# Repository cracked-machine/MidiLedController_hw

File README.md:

# MIDI LED Controller (HW)

Required Kicad Hardware library: https://github.com/cracked-machine/KicadLibrary

For the corresponding SW repository:
[MidiLedController_sw](https://github.com/cracked-machine/MidiLedController_sw)

## Detailed Specifications:

Power Supply: 12V @ 2A (center positive).
Total quiescent current consumption: 85mA
Voltage output per channel: 10V
Current output per channel (Nom.): 
Total current consumption (Nom.): 
Current output per channel (fault limit): 
Total current consumption (fault limit): 2A

 ## Theory of Operation

 ### Power Supply overview

 A 12V DC input supply is stepped-down to 10V. Most of this will be used to power the LEDs. This is regulated down to provide 5V @ 100mA for the status leds. Additionally 3.3V @ 20mA is provided to the microcontroller.

### Output Channel overview

 MIDI Note-On commands are received and synchronised with the gating of 9 independant LED output channels.
 The brightness of all 9 channels can be adjusted simultaneously at the rear of the module.

 Fault protection monitors each output channel for short-circuit and over-current conditions.
 Fault protection is done on the _high side_ of the switch. MIDI data transmission is done on the _low side_ of the switch. i.e. the output channel anode remains at 5V (during normal operation) while the cathode is toggled by the Microcontroller GPIO.

 Individual output channel status is indicated with a tricolour LED.  See details on the Status LED sub-system below.

### Output channel status LED statemachine

Each output channel has a tricolour LED. As before a _green_ LED indicates that a load is connected to the output channel and power delivery to that channel is functioning as normal. An overcurrent or short circuit event is indicated by a _red_ LED and all power is disabled from that output channel.

A _blue_ LED indicates that no load is connected to the output channel. At this point, if MIDI data is still being transferred to that channel, the status LED will alternate between green and blue, in sync with the received MIDI data. This allows testing of the MIDI data transmission without needing to connect a load to the output channel.

When the load is connected, the status LED will **always** remain solid _green_.

A _red_ power fault status such as over current or short circuit will **always** override the other status colours.

### TODO

* upgrade SMPS to drop-in 3A components (TP56339, TPS54302, TPS54309). Considerations are Fsw/L1 size, Thermal Limits and cooling.
* Upgrade output series SOT23 transistor to higher currrent/thermal limit component...or to larger component (SOT223?)
* Test audio input triggering
* Additional pot control for reset delay (dual gang/ concetric pot)
* Upgrade DIP4 to DIP6

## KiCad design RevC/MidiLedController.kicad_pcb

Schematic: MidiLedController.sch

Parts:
C5, C26: 100pF; C_0805_2012Metric_Pad1.15x1.40mm_HandSolder; LcscNo C152892
C6, C28: 100n; C_0805_2012Metric_Pad1.15x1.40mm_HandSolder; LcscNo C94108
C32: 4.7u; C_0805_2012Metric_Pad1.15x1.40mm_HandSolder; LcscNo C87998
C33: 10n; C_0805_2012Metric_Pad1.15x1.40mm_HandSolder; LcscNo C107135
C34: 1u; C_0805_2012Metric_Pad1.15x1.40mm_HandSolder; LcscNo C376927
D2: 1N4148; D_SOD-323_HandSoldering; MouserNo 583-FM4005-T
D_STATUS1: LED_RAGB; LED_D5.0mm-4_RGB_Wide_Pins
D_STATUS_2, D_STATUS_3, D_STATUS_4, D_STATUS_5, D_STATUS_6, D_STATUS_7, D_STATUS_8, D_STATUS_9: LED_RAGB; LED_D5.0mm-4_RGB_Wide_Pins
J1: Molex 2Way KK254; PinHeader_1x05_P2.54mm_Vertical
J12: Barrel_Jack; BarrelJack_Horizontal
J_AUX1: Conn_01x04; PinHeader_1x04_P2.54mm_Vertical
J_MIDI_IN1: DIN-5; RS_5P180_DIN5_SOCKET_WSHIELD
J_OUT1, J_OUT2, J_OUT3, J_OUT4, J_OUT5, J_OUT6, J_OUT7, J_OUT8, J_OUT9: Barrel_Jack_Switch; BarrelJack_Horizontal
R1: 10K; R_0805_2012Metric_Pad1.15x1.40mm_HandSolder; LcscNo C115295
R4: 220R; R_0805_2012Metric_Pad1.15x1.40mm_HandSolder; MouserNo 71-CRCW0805220RFKEAC
R9: 4K7; R_0805_2012Metric_Pad1.15x1.40mm_HandSolder; MouserNo 279-CRGP0805F270R
R25, R74: 100R; R_0805_2012Metric_Pad1.15x1.40mm_HandSolder; LcscNo C106949
R119, R120, R121, R122: 1K; R_0805_2012Metric_Pad1.15x1.40mm_HandSolder; LcscNo C25623
RV1: PTH901; MouserNo 652-PTH901-030S-103B
SW1: SW_DIP_x04; SW_DIP_SPSTx04_Slide_6.7x11.72mm_W7.62mm_P2.54mm_LowProfile
SW2: SW_SPST; SW_Tactile_SPST_Angled_PTS645Vx31-2LFS
TP1, TP3, TP4, TP7, TP19, TP42, TP44, TP46, TP50: TestPoint; TestPoint_Pad_1.0x1.0mm
U19: H11L1; SMDIP-6_W9.53mm
U20: STM32F051K8Tx; LQFP-32_7x7mm_P0.8mm; MouserNo 511-STM32F051K8T6

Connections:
+3.3VA: C33.1, C34.1, U20.5 (VDDA); also elsewhere on the board
+3V3: C6.1, C28.1, C32.1, J1.1, R119.1, R120.1, R121.1, R122.1, RV1.3, RV1.6, U20.1 (VDD), U20.17 (VDD); also elsewhere on the board
+5V: J_AUX1.4, R9.1, U19.6; also elsewhere on the board
/ADC_IN0: C26.2, R74.2, TP1.1, U20.6 (PA0)
/ADC_IN1: C5.2, R25.2, TP3.1, U20.7 (PA1)
/ADC_IN2: J_AUX1.2, U20.8 (PA2)
/ADC_IN3: J_AUX1.1, U20.9 (PA3)
/CH1_PWR: J_OUT1.1; also elsewhere on the board
/CH2_PWR: J_OUT2.1; also elsewhere on the board
/CH3_PWR: J_OUT3.1; also elsewhere on the board
/CH4_PWR: J_OUT4.1; also elsewhere on the board
/CH5_PWR: J_OUT5.1; also elsewhere on the board
/CH6_PWR: J_OUT6.1; also elsewhere on the board
/CH7_PWR: J_OUT7.1; also elsewhere on the board
/CH8_PWR: J_OUT8.1; also elsewhere on the board
/CH9_PWR: J_OUT9.1; also elsewhere on the board
/CONFIG1: R119.2, SW1.8, U20.10 (PA4)
/CONFIG2: R120.2, SW1.7, U20.11 (PA5)
/CONFIG3: R121.2, SW1.6, U20.12 (PA6)
/CONFIG4: R122.2, SW1.5, U20.13 (PA7)
/ChannelNMOS1/CH_CATHODE: J_OUT1.2; also elsewhere on the board
/ChannelNMOS2/CH_CATHODE: J_OUT2.2; also elsewhere on the board
/ChannelNMOS3/CH_CATHODE: J_OUT3.2; also elsewhere on the board
/ChannelNMOS4/CH_CATHODE: J_OUT4.2; also elsewhere on the board
/ChannelNMOS5/CH_CATHODE: J_OUT5.2; also elsewhere on the board
/ChannelNMOS6/CH_CATHODE: J_OUT6.2; also elsewhere on the board
/ChannelNMOS7/CH_CATHODE: J_OUT7.2; also elsewhere on the board
/ChannelNMOS8/CH_CATHODE: J_OUT8.2; also elsewhere on the board
/ChannelNMOS9/CH_CATHODE: J_OUT9.2; also elsewhere on the board
/ChannelStatusLED1/CH_DISABLE_SW: J_OUT1.3; also elsewhere on the board
/ChannelStatusLED1/CH_LED1: D_STATUS1.1 (RK); also elsewhere on the board
/ChannelStatusLED1/CH_LED3: D_STATUS1.3 (GK); also elsewhere on the board
/ChannelStatusLED1/CH_LED4: D_STATUS1.4 (BK); also elsewhere on the board
/ChannelStatusLED2/CH_DISABLE_SW: J_OUT2.3; also elsewhere on the board
/ChannelStatusLED2/CH_LED1: D_STATUS_2.1 (RK); also elsewhere on the board
/ChannelStatusLED2/CH_LED3: D_STATUS_2.3 (GK); also elsewhere on the board
/ChannelStatusLED2/CH_LED4: D_STATUS_2.4 (BK); also elsewhere on the board
/ChannelStatusLED3/CH_DISABLE_SW: J_OUT3.3; also elsewhere on the board
/ChannelStatusLED3/CH_LED1: D_STATUS_3.1 (RK); also elsewhere on the board
/ChannelStatusLED3/CH_LED3: D_STATUS_3.3 (GK); also elsewhere on the board
/ChannelStatusLED3/CH_LED4: D_STATUS_3.4 (BK); also elsewhere on the board
/ChannelStatusLED4/CH_DISABLE_SW: J_OUT4.3; also elsewhere on the board
/ChannelStatusLED4/CH_LED1: D_STATUS_4.1 (RK); also elsewhere on the board
/ChannelStatusLED4/CH_LED3: D_STATUS_4.3 (GK); also elsewhere on the board
/ChannelStatusLED4/CH_LED4: D_STATUS_4.4 (BK); also elsewhere on the board
/ChannelStatusLED5/CH_DISABLE_SW: J_OUT5.3; also elsewhere on the board
/ChannelStatusLED5/CH_LED1: D_STATUS_5.1 (RK); also elsewhere on the board
/ChannelStatusLED5/CH_LED3: D_STATUS_5.3 (GK); also elsewhere on the board
/ChannelStatusLED5/CH_LED4: D_STATUS_5.4 (BK); also elsewhere on the board
/ChannelStatusLED6/CH_DISABLE_SW: J_OUT6.3; also elsewhere on the board
/ChannelStatusLED6/CH_LED1: D_STATUS_6.1 (RK); also elsewhere on the board
/ChannelStatusLED6/CH_LED3: D_STATUS_6.3 (GK); also elsewhere on the board
/ChannelStatusLED6/CH_LED4: D_STATUS_6.4 (BK); also elsewhere on the board
/ChannelStatusLED7/CH_DISABLE_SW: J_OUT7.3; also elsewhere on the board
/ChannelStatusLED7/CH_LED1: D_STATUS_7.1 (RK); also elsewhere on the board
/ChannelStatusLED7/CH_LED3: D_STATUS_7.3 (GK); also elsewhere on the board
/ChannelStatusLED7/CH_LED4: D_STATUS_7.4 (BK); also elsewhere on the board
/ChannelStatusLED8/CH_DISABLE_SW: J_OUT8.3; also elsewhere on the board
/ChannelStatusLED8/CH_LED1: D_STATUS_8.1 (RK); also elsewhere on the board
/ChannelStatusLED8/CH_LED3: D_STATUS_8.3 (GK); also elsewhere on the board
/ChannelStatusLED8/CH_LED4: D_STATUS_8.4 (BK); also elsewhere on the board
/ChannelStatusLED9/CH_DISABLE_SW: J_OUT9.3; also elsewhere on the board
/ChannelStatusLED9/CH_LED1: D_STATUS_9.1 (RK); also elsewhere on the board
/ChannelStatusLED9/CH_LED3: D_STATUS_9.3 (GK); also elsewhere on the board
/ChannelStatusLED9/CH_LED4: D_STATUS_9.4 (BK); also elsewhere on the board
/MIDI_RX: R9.2, TP4.1, U19.5, U20.30 (PB7)
/NRST: J1.5, U20.4 (NRST)
/PowerSupply/ENSW: SW2.2 (B); also elsewhere on the board
/PowerSupply/VIN: J12.1; also elsewhere on the board
/STATUS1_ANODE: D_STATUS1.2 (A); also elsewhere on the board
/STATUS2_ANODE: D_STATUS_2.2 (A); also elsewhere on the board
/STATUS3_ANODE: D_STATUS_3.2 (A); also elsewhere on the board
/STATUS4_ANODE: D_STATUS_4.2 (A); also elsewhere on the board
/STATUS5_ANODE: D_STATUS_5.2 (A); also elsewhere on the board
/STATUS6_ANODE: D_STATUS_6.2 (A); also elsewhere on the board
/STATUS7_ANODE: D_STATUS_7.2 (A); also elsewhere on the board
/STATUS8_ANODE: D_STATUS_8.2 (A); also elsewhere on the board
/STATUS9_ANODE: D_STATUS_9.2 (A); also elsewhere on the board
/SWCLK: J1.2, U20.24 (PA14)
/SWDIO: J1.4, U20.23 (PA13)
/TIM1_CH1: U20.18 (PA8); also elsewhere on the board
/TIM1_CH2: U20.19 (PA9); also elsewhere on the board
/TIM1_CH3: U20.20 (PA10); also elsewhere on the board
/TIM2_CH1: U20.25 (PA15); also elsewhere on the board
/TIM2_CH2: U20.26 (PB3); also elsewhere on the board
/TIM3_CH1: U20.27 (PB4); also elsewhere on the board
/TIM3_CH2: U20.28 (PB5); also elsewhere on the board
/TIM3_CH3: U20.14 (PB0); also elsewhere on the board
/TIM3_CH4: U20.15 (PB1); also elsewhere on the board
GNDS: C5.1, C6.2, C26.1, C28.2, C32.2, C33.2, C34.2, J1.3, J12.2, J_AUX1.3, R1.2, RV1.1, RV1.4, SW1.1, SW1.2, SW1.3, SW1.4, SW2.1 (A), TP19.1, TP42.1, TP44.1, TP46.1, TP50.1, U19.4, U20.16 (VSS), U20.32 (VSS); also elsewhere on the board
unnamed: D2.1 (K), R4.1, U19.1
unnamed: D2.2 (A), J_MIDI_IN1.5, U19.3
unnamed: J_MIDI_IN1.4, R4.2, TP7.1
unnamed: R1.1, U20.31 (BOOT0)
unnamed: R25.1, RV1.5
unnamed: R74.1, RV1.2

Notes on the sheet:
ICSP
MicroController
USART TX (NOT USED)
MIDI Input
Power Supply / Regulation
Brightness Control
5-12V POWER INPUT
Output Channel 1
Output Channel 2
Output Channel 3
Output Channel 4
Output Channel 5
Output Channel 6
Output Channel 7
Output Channel 8
Output Channel 9
(RED) (ANODE) (GREEN) (BLUE)
LED STRIP
change to 270R if using 6N137
Config Switches

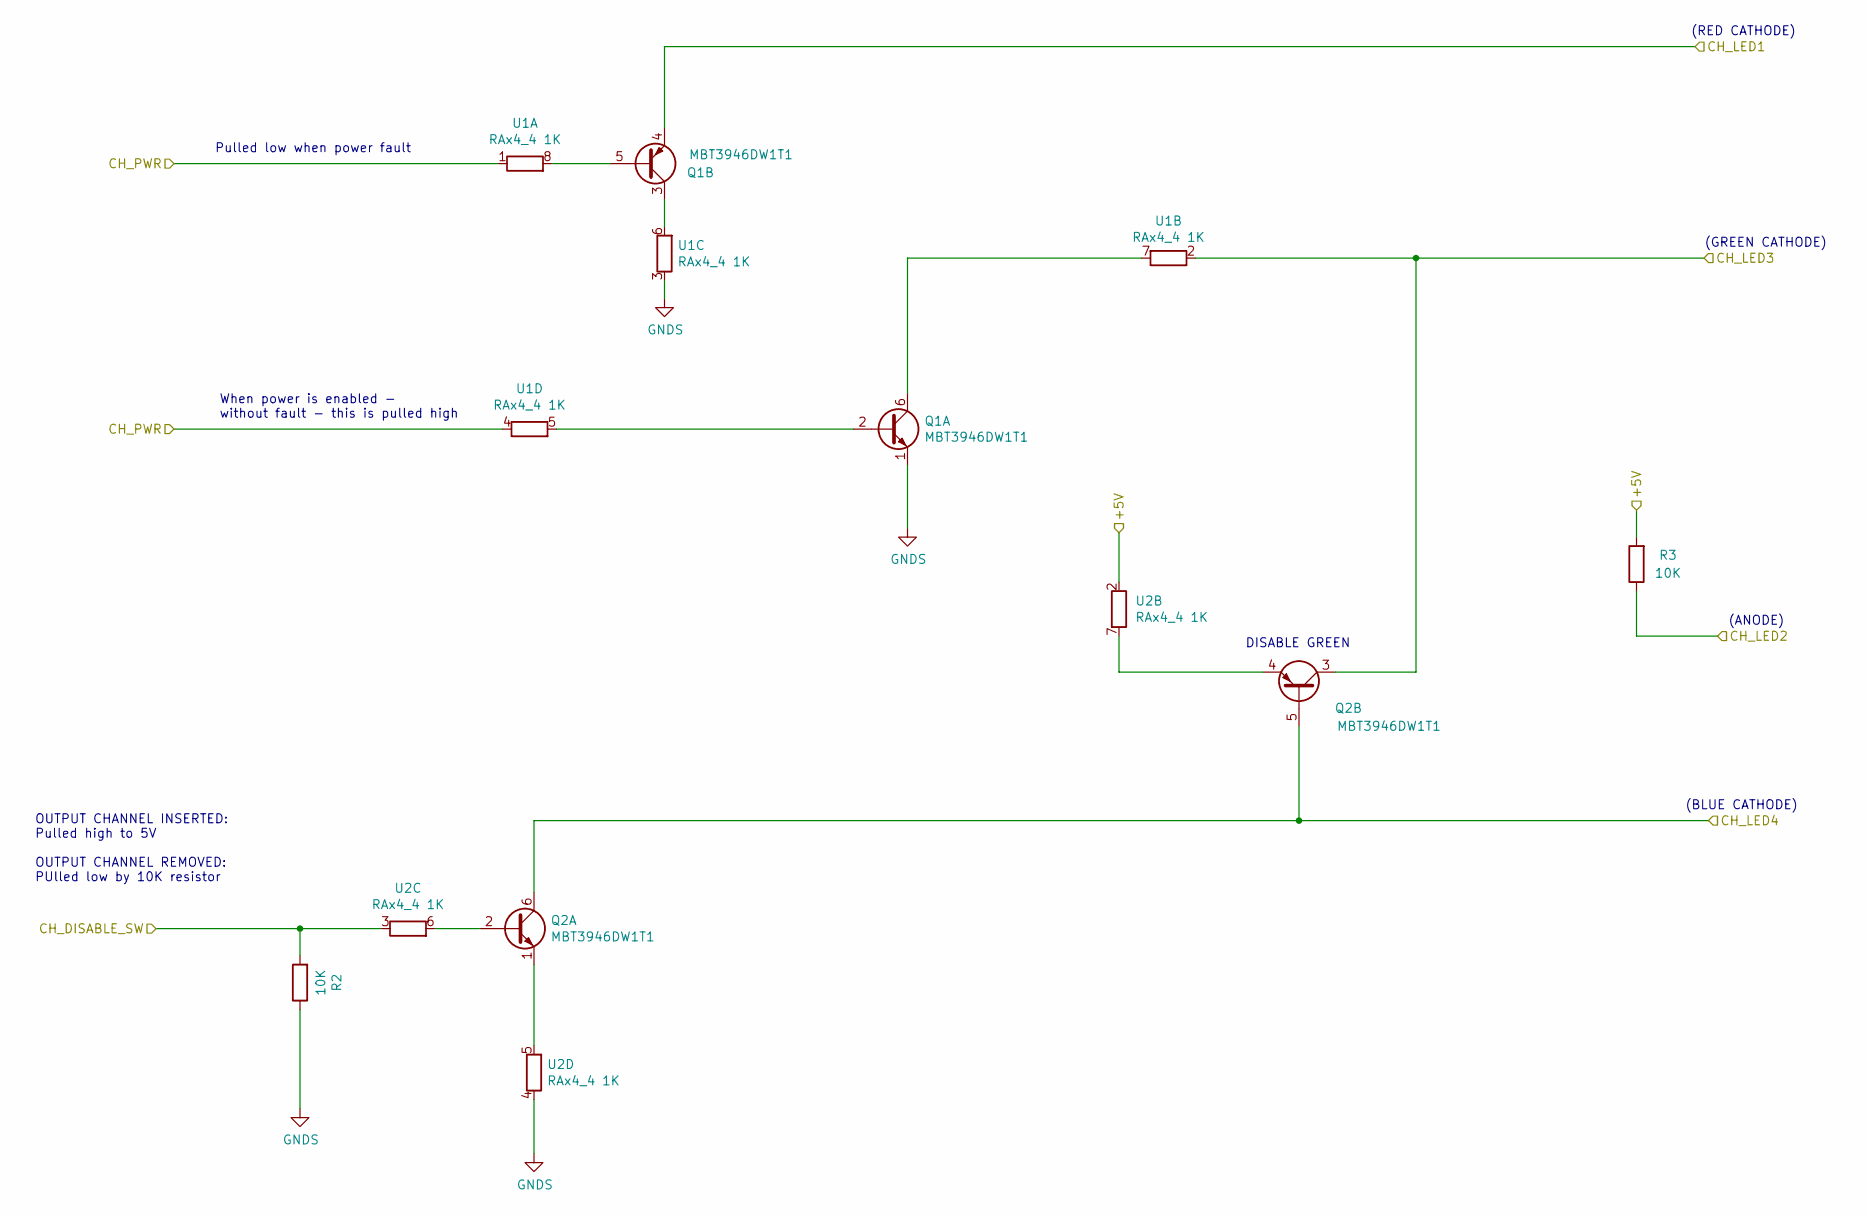
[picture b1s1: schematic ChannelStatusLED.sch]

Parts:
Q1, Q2: MBT3946DW1T1; SOT-363_SC-70-6
R2, R3: 10K; R_0805_2012Metric_Pad1.15x1.40mm_HandSolder; LcscNo C115295
U1, U2: RAx4_4 1K; R_Array_Convex_4x0603; LcscNo C396839

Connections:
+5V: R3.2, U2.2; also elsewhere on the board
/CH1_PWR: U1.1, U1.4; also elsewhere on the board
/ChannelStatusLED1/CH_DISABLE_SW: R2.2, U2.3; also elsewhere on the board
/ChannelStatusLED1/CH_LED1: Q1.4 (E2); also elsewhere on the board
/ChannelStatusLED1/CH_LED3: Q2.3 (C2), U1.2; also elsewhere on the board
/ChannelStatusLED1/CH_LED4: Q2.5 (B2), Q2.6 (C1); also elsewhere on the board
/STATUS1_ANODE: R3.1; also elsewhere on the board
GNDS: Q1.1 (E1), R2.1, U1.3, U2.4; also elsewhere on the board
unnamed: Q1.2 (B1), U1.5
unnamed: Q1.3 (C2), U1.6
unnamed: Q1.5 (B2), U1.8
unnamed: Q1.6 (C1), U1.7
unnamed: Q2.1 (E1), U2.5
unnamed: Q2.2 (B1), U2.6
unnamed: Q2.4 (E2), U2.7

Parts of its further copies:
Q3, Q4, Q5, Q6, Q7, Q8, Q9, Q10, Q11, Q12, Q13, Q14, Q15, Q16, Q17, Q18: MBT3946DW1T1; SOT-363_SC-70-6
R5, R6, R7, R8, R10, R11, R12, R14, R17, R18, R19, R20, R21, R22, R23, R24: 10K; R_0805_2012Metric_Pad1.15x1.40mm_HandSolder; LcscNo C115295
U3, U4, U5, U6, U7, U8, U9, U10, U11, U12, U13, U14, U15, U16, U17, U18: RAx4_4 1K; R_Array_Convex_4x0603; LcscNo C396839

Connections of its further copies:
+5V: R6.2, R8.2, R11.2, R14.2, R18.2, R20.2, R22.2, R24.2, U4.1, U4.2, U6.1, U6.2, U8.1, U8.2, U10.1, U10.2, U12.1, U12.2, U14.1, U14.2, U16.1, U16.2, U18.1, U18.2; also elsewhere on the board
/CH2_PWR: U3.1, U3.4; also elsewhere on the board
/CH3_PWR: U5.1, U5.4; also elsewhere on the board
/CH4_PWR: U7.1, U7.4; also elsewhere on the board
/CH5_PWR: U9.1, U9.4; also elsewhere on the board
/CH6_PWR: U11.1, U11.4; also elsewhere on the board
/CH7_PWR: U13.1, U13.4; also elsewhere on the board
/CH8_PWR: U15.1, U15.4; also elsewhere on the board
/CH9_PWR: U17.1, U17.4; also elsewhere on the board
/ChannelNMOS2/CH_CATHODE: U4.8; also elsewhere on the board
/ChannelNMOS3/CH_CATHODE: U6.8; also elsewhere on the board
/ChannelNMOS4/CH_CATHODE: U8.8; also elsewhere on the board
/ChannelNMOS5/CH_CATHODE: U10.8; also elsewhere on the board
/ChannelNMOS6/CH_CATHODE: U12.8; also elsewhere on the board
/ChannelNMOS7/CH_CATHODE: U14.8; also elsewhere on the board
/ChannelNMOS8/CH_CATHODE: U16.8; also elsewhere on the board
/ChannelNMOS9/CH_CATHODE: U18.8; also elsewhere on the board
/ChannelStatusLED2/CH_DISABLE_SW: R5.2, U4.3; also elsewhere on the board
/ChannelStatusLED2/CH_LED1: Q3.4 (E2); also elsewhere on the board
/ChannelStatusLED2/CH_LED3: Q4.3 (C2), U3.2; also elsewhere on the board
/ChannelStatusLED2/CH_LED4: Q4.5 (B2), Q4.6 (C1); also elsewhere on the board
/ChannelStatusLED3/CH_DISABLE_SW: R7.2, U6.3; also elsewhere on the board
/ChannelStatusLED3/CH_LED1: Q5.4 (E2); also elsewhere on the board
/ChannelStatusLED3/CH_LED3: Q6.3 (C2), U5.2; also elsewhere on the board
/ChannelStatusLED3/CH_LED4: Q6.5 (B2), Q6.6 (C1); also elsewhere on the board
/ChannelStatusLED4/CH_DISABLE_SW: R10.2, U8.3; also elsewhere on the board
/ChannelStatusLED4/CH_LED1: Q7.4 (E2); also elsewhere on the board
/ChannelStatusLED4/CH_LED3: Q8.3 (C2), U7.2; also elsewhere on the board
/ChannelStatusLED4/CH_LED4: Q8.5 (B2), Q8.6 (C1); also elsewhere on the board
/ChannelStatusLED5/CH_DISABLE_SW: R12.2, U10.3; also elsewhere on the board
/ChannelStatusLED5/CH_LED1: Q9.4 (E2); also elsewhere on the board
/ChannelStatusLED5/CH_LED3: Q10.3 (C2), U9.2; also elsewhere on the board
/ChannelStatusLED5/CH_LED4: Q10.5 (B2), Q10.6 (C1); also elsewhere on the board
/ChannelStatusLED6/CH_DISABLE_SW: R17.2, U12.3; also elsewhere on the board
/ChannelStatusLED6/CH_LED1: Q11.4 (E2); also elsewhere on the board
/ChannelStatusLED6/CH_LED3: Q12.3 (C2), U11.2; also elsewhere on the board
/ChannelStatusLED6/CH_LED4: Q12.5 (B2), Q12.6 (C1); also elsewhere on the board
/ChannelStatusLED7/CH_DISABLE_SW: R19.2, U14.3; also elsewhere on the board
/ChannelStatusLED7/CH_LED1: Q13.4 (E2); also elsewhere on the board
/ChannelStatusLED7/CH_LED3: Q14.3 (C2), U13.2; also elsewhere on the board
/ChannelStatusLED7/CH_LED4: Q14.5 (B2), Q14.6 (C1); also elsewhere on the board
/ChannelStatusLED8/CH_DISABLE_SW: R21.2, U16.3; also elsewhere on the board
/ChannelStatusLED8/CH_LED1: Q15.4 (E2); also elsewhere on the board
/ChannelStatusLED8/CH_LED3: Q16.3 (C2), U15.2; also elsewhere on the board
/ChannelStatusLED8/CH_LED4: Q16.5 (B2), Q16.6 (C1); also elsewhere on the board
/ChannelStatusLED9/CH_DISABLE_SW: R23.2, U18.3; also elsewhere on the board
/ChannelStatusLED9/CH_LED1: Q17.4 (E2); also elsewhere on the board
/ChannelStatusLED9/CH_LED3: Q18.3 (C2), U17.2; also elsewhere on the board
/ChannelStatusLED9/CH_LED4: Q18.5 (B2), Q18.6 (C1); also elsewhere on the board
/STATUS2_ANODE: R6.1; also elsewhere on the board
/STATUS3_ANODE: R8.1; also elsewhere on the board
/STATUS4_ANODE: R11.1; also elsewhere on the board
/STATUS5_ANODE: R14.1; also elsewhere on the board
/STATUS6_ANODE: R18.1; also elsewhere on the board
/STATUS7_ANODE: R20.1; also elsewhere on the board
/STATUS8_ANODE: R22.1; also elsewhere on the board
/STATUS9_ANODE: R24.1; also elsewhere on the board
GNDS: Q3.1 (E1), Q5.1 (E1), Q7.1 (E1), Q9.1 (E1), Q11.1 (E1), Q13.1 (E1), Q15.1 (E1), Q17.1 (E1), R5.1, R7.1, R10.1, R12.1, R17.1, R19.1, R21.1, R23.1, U3.3, U4.4, U5.3, U6.4, U7.3, U8.4, U9.3, U10.4, U11.3, U12.4, U13.3, U14.4, U15.3, U16.4, U17.3, U18.4; also elsewhere on the board
unnamed: Q3.2 (B1), U3.5
unnamed: Q3.3 (C2), U3.6
unnamed: Q3.5 (B2), U3.8
unnamed: Q3.6 (C1), U3.7
unnamed: Q4.1 (E1), U4.5
unnamed: Q4.2 (B1), U4.6
unnamed: Q4.4 (E2), U4.7
unnamed: Q5.2 (B1), U5.5
unnamed: Q5.3 (C2), U5.6
unnamed: Q5.5 (B2), U5.8
unnamed: Q5.6 (C1), U5.7
unnamed: Q6.1 (E1), U6.5
unnamed: Q6.2 (B1), U6.6
unnamed: Q6.4 (E2), U6.7
unnamed: Q7.2 (B1), U7.5
unnamed: Q7.3 (C2), U7.6
unnamed: Q7.5 (B2), U7.8
unnamed: Q7.6 (C1), U7.7
unnamed: Q8.1 (E1), U8.5
unnamed: Q8.2 (B1), U8.6
unnamed: Q8.4 (E2), U8.7
unnamed: Q9.2 (B1), U9.5
unnamed: Q9.3 (C2), U9.6
unnamed: Q9.5 (B2), U9.8
unnamed: Q9.6 (C1), U9.7
unnamed: Q10.1 (E1), U10.5
unnamed: Q10.2 (B1), U10.6
unnamed: Q10.4 (E2), U10.7
unnamed: Q11.2 (B1), U11.5
unnamed: Q11.3 (C2), U11.6
unnamed: Q11.5 (B2), U11.8
unnamed: Q11.6 (C1), U11.7
unnamed: Q12.1 (E1), U12.5
unnamed: Q12.2 (B1), U12.6
unnamed: Q12.4 (E2), U12.7
unnamed: Q13.2 (B1), U13.5
unnamed: Q13.3 (C2), U13.6
unnamed: Q13.5 (B2), U13.8
unnamed: Q13.6 (C1), U13.7
unnamed: Q14.1 (E1), U14.5
unnamed: Q14.2 (B1), U14.6
unnamed: Q14.4 (E2), U14.7
unnamed: Q15.2 (B1), U15.5
unnamed: Q15.3 (C2), U15.6
unnamed: Q15.5 (B2), U15.8
unnamed: Q15.6 (C1), U15.7
unnamed: Q16.1 (E1), U16.5
unnamed: Q16.2 (B1), U16.6
unnamed: Q16.4 (E2), U16.7
unnamed: Q17.2 (B1), U17.5
unnamed: Q17.3 (C2), U17.6
unnamed: Q17.5 (B2), U17.8
unnamed: Q17.6 (C1), U17.7
unnamed: Q18.1 (E1), U18.5
unnamed: Q18.2 (B1), U18.6
unnamed: Q18.4 (E2), U18.7

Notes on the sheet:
When power is enabled - without fault - this is pulled high
(BLUE CATHODE)
(ANODE)
(GREEN CATHODE)
Pulled low when power fault
(RED CATHODE)
DISABLE GREEN
OUTPUT CHANNEL INSERTED: Pulled high to 5V OUTPUT CHANNEL REMOVED: PUlled low by 10K resistor

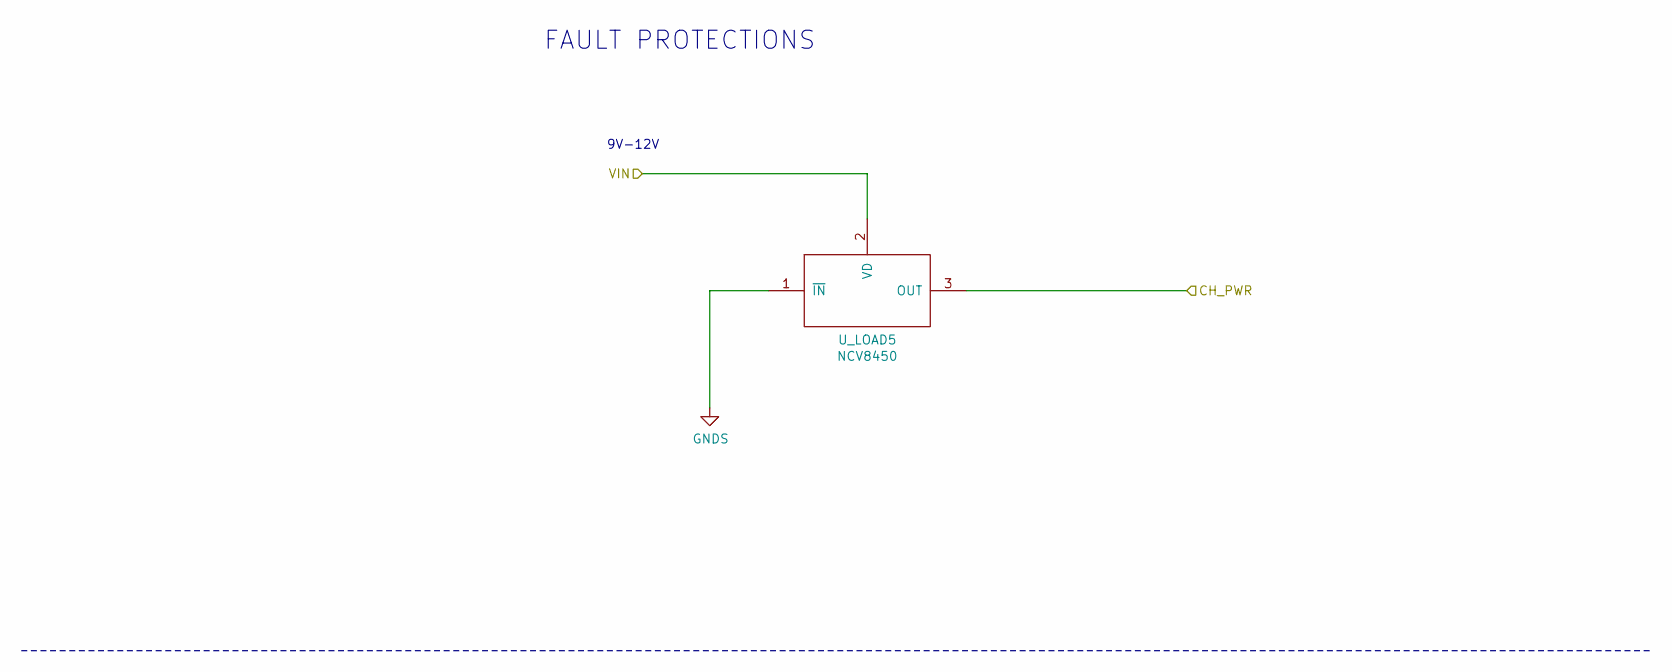
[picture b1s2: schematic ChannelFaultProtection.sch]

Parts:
U_LOAD2: NCV8450; SOT-223-3_TabPin2; LcscNo C100028

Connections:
/CH2_PWR: U_LOAD2.3 (OUT); also elsewhere on the board
GNDS: U_LOAD2.1 (~IN); also elsewhere on the board
VPP: U_LOAD2.2 (VD); also elsewhere on the board

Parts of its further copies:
U_LOAD1, U_LOAD3, U_LOAD4, U_LOAD5, U_LOAD6, U_LOAD7, U_LOAD8, U_LOAD9: NCV8450; SOT-223-3_TabPin2; LcscNo C100028

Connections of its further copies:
/CH1_PWR: U_LOAD1.3 (OUT); also elsewhere on the board
/CH3_PWR: U_LOAD3.3 (OUT); also elsewhere on the board
/CH4_PWR: U_LOAD4.3 (OUT); also elsewhere on the board
/CH5_PWR: U_LOAD5.3 (OUT); also elsewhere on the board
/CH6_PWR: U_LOAD6.3 (OUT); also elsewhere on the board
/CH7_PWR: U_LOAD7.3 (OUT); also elsewhere on the board
/CH8_PWR: U_LOAD8.3 (OUT); also elsewhere on the board
/CH9_PWR: U_LOAD9.3 (OUT); also elsewhere on the board
GNDS: U_LOAD1.1 (~IN), U_LOAD3.1 (~IN), U_LOAD4.1 (~IN), U_LOAD5.1 (~IN), U_LOAD6.1 (~IN), U_LOAD7.1 (~IN), U_LOAD8.1 (~IN), U_LOAD9.1 (~IN); also elsewhere on the board
VPP: U_LOAD1.2 (VD), U_LOAD3.2 (VD), U_LOAD4.2 (VD), U_LOAD5.2 (VD), U_LOAD6.2 (VD), U_LOAD7.2 (VD), U_LOAD8.2 (VD), U_LOAD9.2 (VD); also elsewhere on the board

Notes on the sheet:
9V-12V
FAULT PROTECTIONS

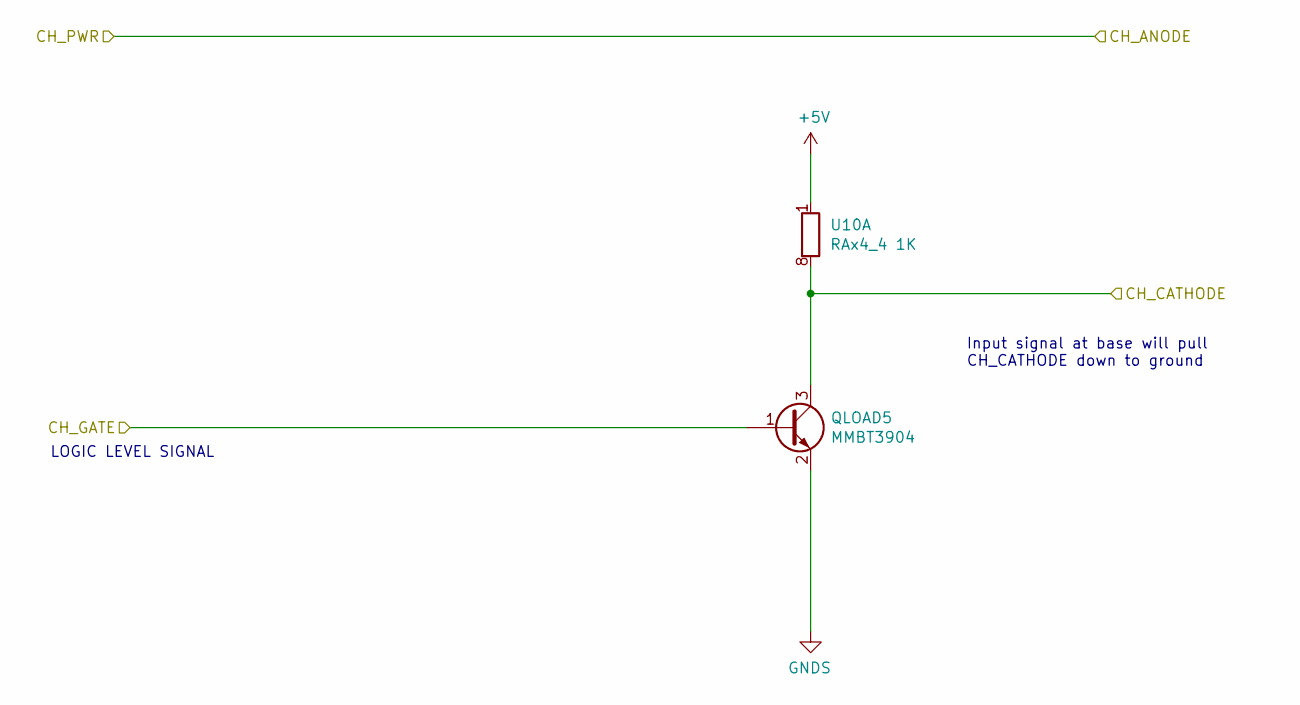
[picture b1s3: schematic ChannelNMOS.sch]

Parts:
QLOAD1: MMBT3904; SOT-23; LcscNo C20526
U2: RAx4_4 1K; R_Array_Convex_4x0603

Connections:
+5V: U2.1; also elsewhere on the board
/ChannelNMOS1/CH_CATHODE: QLOAD1.3 (C), U2.8; also elsewhere on the board
/TIM2_CH1: QLOAD1.1 (B); also elsewhere on the board
GNDS: QLOAD1.2 (E); also elsewhere on the board

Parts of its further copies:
QLOAD2, QLOAD3, QLOAD4, QLOAD5, QLOAD6, QLOAD7, QLOAD8, QLOAD9: MMBT3904; SOT-23; LcscNo C20526
U4, U6, U8, U10, U12, U14, U16, U18: RAx4_4 1K; R_Array_Convex_4x0603

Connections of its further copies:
+5V: U4.1, U4.2, U6.1, U6.2, U8.1, U8.2, U10.1, U10.2, U12.1, U12.2, U14.1, U14.2, U16.1, U16.2, U18.1, U18.2; also elsewhere on the board
/ChannelNMOS2/CH_CATHODE: QLOAD2.3 (C), U4.8; also elsewhere on the board
/ChannelNMOS3/CH_CATHODE: QLOAD3.3 (C), U6.8; also elsewhere on the board
/ChannelNMOS4/CH_CATHODE: QLOAD4.3 (C), U8.8; also elsewhere on the board
/ChannelNMOS5/CH_CATHODE: QLOAD5.3 (C), U10.8; also elsewhere on the board
/ChannelNMOS6/CH_CATHODE: QLOAD6.3 (C), U12.8; also elsewhere on the board
/ChannelNMOS7/CH_CATHODE: QLOAD7.3 (C), U14.8; also elsewhere on the board
/ChannelNMOS8/CH_CATHODE: QLOAD8.3 (C), U16.8; also elsewhere on the board
/ChannelNMOS9/CH_CATHODE: QLOAD9.3 (C), U18.8; also elsewhere on the board
/ChannelStatusLED2/CH_DISABLE_SW: U4.3; also elsewhere on the board
/ChannelStatusLED3/CH_DISABLE_SW: U6.3; also elsewhere on the board
/ChannelStatusLED4/CH_DISABLE_SW: U8.3; also elsewhere on the board
/ChannelStatusLED5/CH_DISABLE_SW: U10.3; also elsewhere on the board
/ChannelStatusLED6/CH_DISABLE_SW: U12.3; also elsewhere on the board
/ChannelStatusLED7/CH_DISABLE_SW: U14.3; also elsewhere on the board
/ChannelStatusLED8/CH_DISABLE_SW: U16.3; also elsewhere on the board
/ChannelStatusLED9/CH_DISABLE_SW: U18.3; also elsewhere on the board
/TIM1_CH1: QLOAD7.1 (B); also elsewhere on the board
/TIM1_CH2: QLOAD8.1 (B); also elsewhere on the board
/TIM1_CH3: QLOAD9.1 (B); also elsewhere on the board
/TIM2_CH2: QLOAD2.1 (B); also elsewhere on the board
/TIM3_CH1: QLOAD3.1 (B); also elsewhere on the board
/TIM3_CH2: QLOAD4.1 (B); also elsewhere on the board
/TIM3_CH3: QLOAD5.1 (B); also elsewhere on the board
/TIM3_CH4: QLOAD6.1 (B); also elsewhere on the board
GNDS: QLOAD2.2 (E), QLOAD3.2 (E), QLOAD4.2 (E), QLOAD5.2 (E), QLOAD6.2 (E), QLOAD7.2 (E), QLOAD8.2 (E), QLOAD9.2 (E), U4.4, U6.4, U8.4, U10.4, U12.4, U14.4, U16.4, U18.4; also elsewhere on the board
unnamed 112: U4.5; also elsewhere on the board
unnamed 113: U4.6; also elsewhere on the board
unnamed 114: U4.7; also elsewhere on the board
unnamed 119: U6.5; also elsewhere on the board
unnamed 120: U6.6; also elsewhere on the board
unnamed 121: U6.7; also elsewhere on the board
unnamed 126: U8.5; also elsewhere on the board
unnamed 127: U8.6; also elsewhere on the board
unnamed 128: U8.7; also elsewhere on the board
unnamed 133: U10.5; also elsewhere on the board
unnamed 134: U10.6; also elsewhere on the board
unnamed 135: U10.7; also elsewhere on the board
unnamed 140: U12.5; also elsewhere on the board
unnamed 141: U12.6; also elsewhere on the board
unnamed 142: U12.7; also elsewhere on the board
unnamed 147: U14.5; also elsewhere on the board
unnamed 148: U14.6; also elsewhere on the board
unnamed 149: U14.7; also elsewhere on the board
unnamed 154: U16.5; also elsewhere on the board
unnamed 155: U16.6; also elsewhere on the board
unnamed 156: U16.7; also elsewhere on the board
unnamed 161: U18.5; also elsewhere on the board
unnamed 162: U18.6; also elsewhere on the board
unnamed 163: U18.7; also elsewhere on the board

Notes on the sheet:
LOGIC LEVEL SIGNAL
Input signal at base will pull CH_CATHODE down to ground

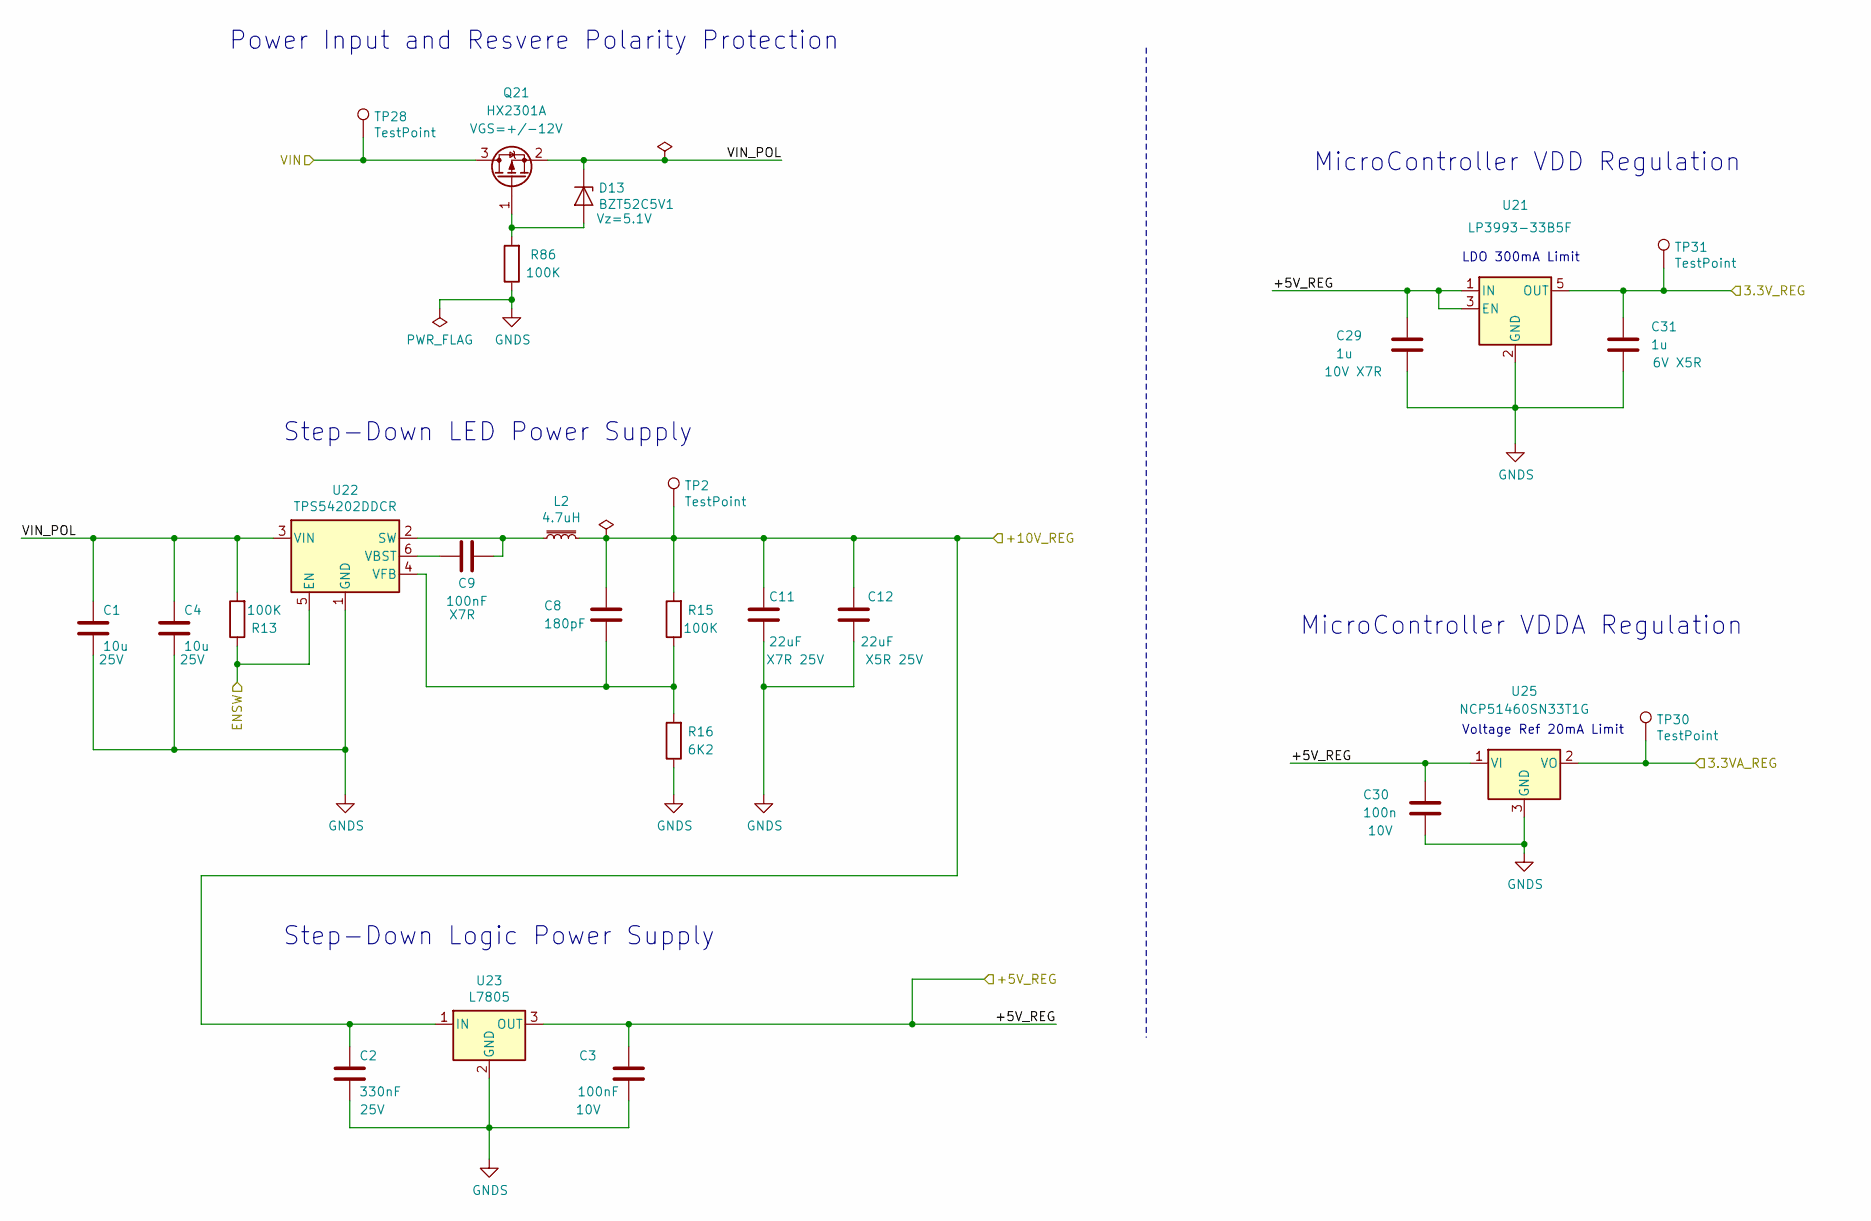
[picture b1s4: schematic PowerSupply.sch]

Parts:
C1, C4: 10u; C_1206_3216Metric_Pad1.42x1.75mm_HandSolder; LcscNo C14860
C2: 330nF; C_1206_3216Metric_Pad1.42x1.75mm_HandSolder; LcscNo C73142
C3: 100nF; C_1206_3216Metric_Pad1.42x1.75mm_HandSolder; LcscNo C94108
C8: 180pF; R_0805_2012Metric_Pad1.15x1.40mm_HandSolder; LcscNo C152881
C9: 100nF; R_0805_2012Metric_Pad1.15x1.40mm_HandSolder; LcscNo C94108
C11, C12: 22uF; C_1206_3216Metric_Pad1.42x1.75mm_HandSolder; LcscNo C268007
C29, C31: 1u; C_0805_2012Metric_Pad1.15x1.40mm_HandSolder; LcscNo C376927
C30: 100n; R_0805_2012Metric_Pad1.15x1.40mm_HandSolder; LcscNo C94108
D13: BZT52C5V1; D_SOD-123; LcscNo C353516
L2: 4.7uH; L_Taiyo-Yuden_NR-80xx_HandSoldering; LcscNo C266428
Q21: HX2301A; SOT-23; LcscNo C296298
R13, R15: 100K; R_0805_2012Metric_Pad1.15x1.40mm_HandSolder; LcscNo C118844
R16: 6K2; R_0805_2012Metric_Pad1.15x1.40mm_HandSolder; MouserNo 71-CRCW080510K0FKEAC
R86: 100K; R_1206_3216Metric_Pad1.42x1.75mm_HandSolder; LcscNo C118844
TP2, TP28, TP30, TP31: TestPoint; TestPoint_Pad_1.0x1.0mm
U21: LP3993-33B5F; SOT-23-5
U22: TPS54202DDCR; SOT-23-6; LcscNo C191884
U23: L7805; TO-263-2; LcscNo C15077
U25: NCP51460SN33T1G; SOT-23; MouserNo 863-NCP51460SN33T1G

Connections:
+3.3VA: TP30.1, U25.2 (VO); also elsewhere on the board
+3V3: C31.1, TP31.1, U21.5 (OUT); also elsewhere on the board
+5V: C3.1, C29.1, C30.1, U21.1 (IN), U21.3 (EN), U23.3 (OUT), U25.1 (VI); also elsewhere on the board
/PowerSupply/ENSW: R13.1, U22.5 (EN); also elsewhere on the board
/PowerSupply/VIN: Q21.3 (D), TP28.1; also elsewhere on the board
/PowerSupply/VIN_POL: C1.1, C4.1, D13.1 (K), Q21.2 (S), R13.2, U22.3 (VIN)
GNDS: C1.2, C2.2, C3.2, C4.2, C11.2, C12.2, C29.2, C30.2, C31.2, R16.1, R86.1, U21.2 (GND), U22.1 (GND), U23.2 (GND), U25.3 (GND); also elsewhere on the board
unnamed: C8.2, R15.1, R16.2, U22.4 (VFB)
unnamed: C9.1, L2.1, U22.2 (SW)
unnamed: C9.2, U22.6 (VBST)
unnamed: D13.2 (A), Q21.1 (G), R86.2
VPP: C2.1, C8.1, C11.1, C12.1, L2.2, R15.2, TP2.1, U23.1 (IN); also elsewhere on the board

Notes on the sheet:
LDO 300mA Limit
Voltage Ref 20mA Limit
Power Input and Resvere Polarity Protection
Step-Down Logic Power Supply
MicroController VDD Regulation
MicroController VDDA Regulation
Step-Down LED Power Supply

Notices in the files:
RevC/MidiLedController.kicad_pcb:
© C.Sutton
